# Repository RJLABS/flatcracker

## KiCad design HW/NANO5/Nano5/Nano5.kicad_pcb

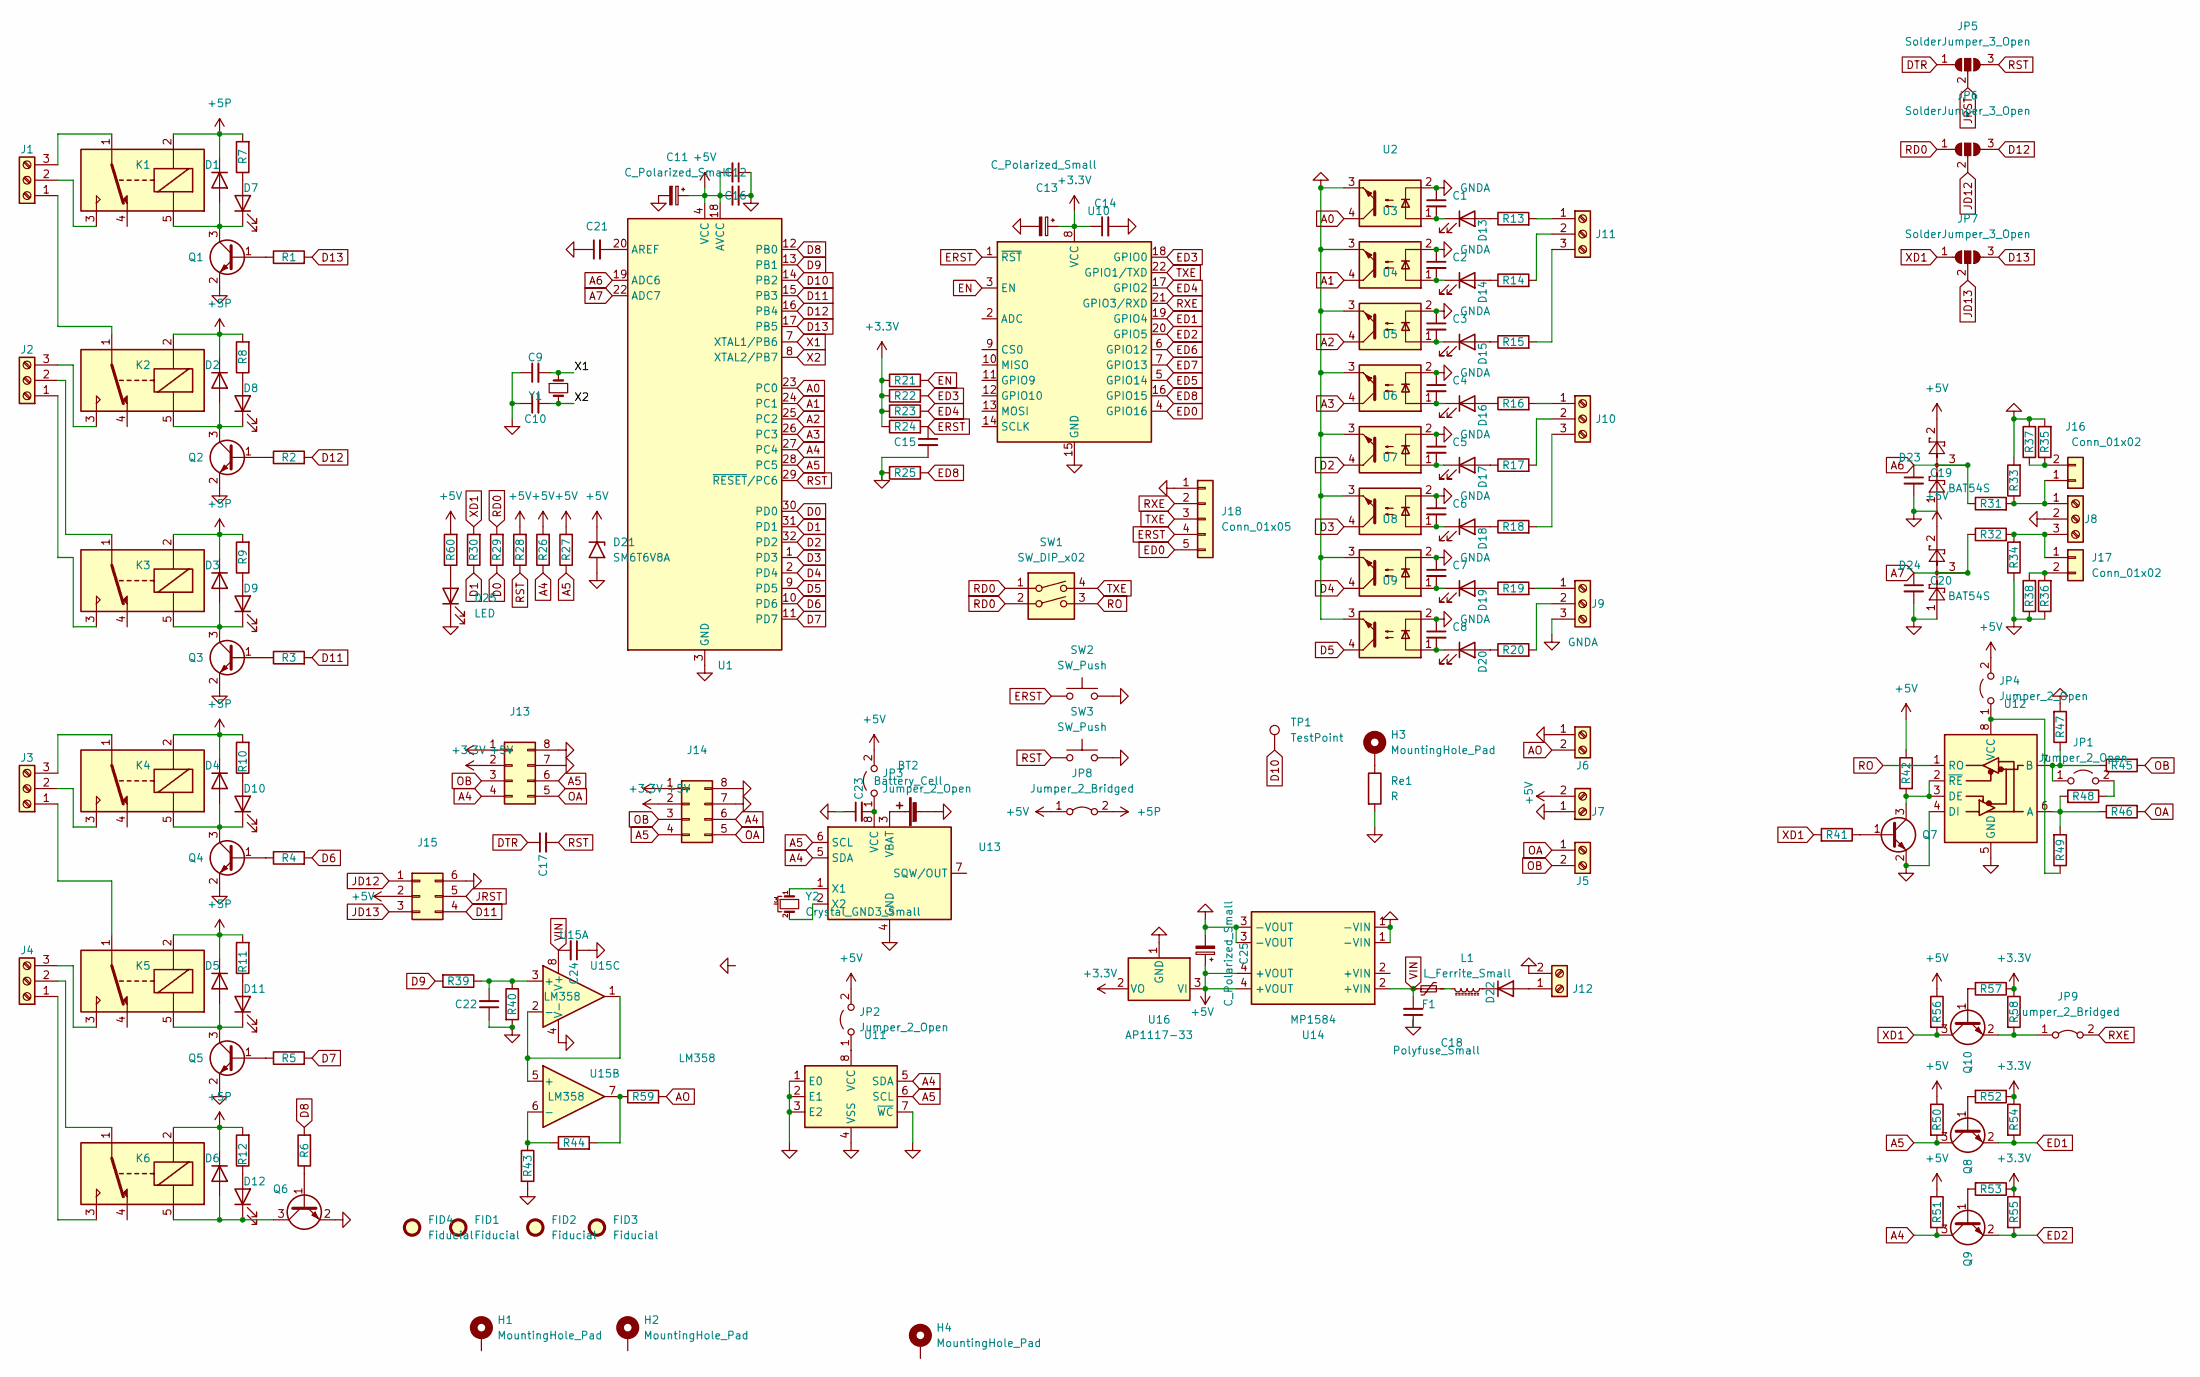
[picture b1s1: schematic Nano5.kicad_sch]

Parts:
BT2: Battery_Cell; BatteryHolder_Keystone_1058_1x2032
C1, C2, C3, C4, C5, C6, C7, C8, C9, C10, C19, C20: C_Small; C_0805_2012Metric
C11, C13, C25: C_Polarized_Small; CP_Elec_4x3.9
C12, C14, C15, C16, C17, C18, C21, C22, C23, C24: 100nF; C_0805_2012Metric
D1, D2, D3, D4, D5, D6, D22: SM4007; D_MELF
D7, D8, D9, D10, D11, D12, D13, D14, D15, D16, D17, D18, D19, D20, D25: LED; LED_0805_2012Metric
D21: SM6T6V8A; D_SMB
D23, D24: BAT54S; SOT-23
F1: Polyfuse_Small; Fuse_1812_4532Metric
FID1, FID2, FID3, FID4: Fiducial; Fiducial_1.5mm_Mask3mm
H1, H2, H3, H4: MountingHole_Pad; MountingHole_3.2mm_M3_Pad_Via
J1, J2, J3, J4, J8, J9, J10, J11: Screw_Terminal_01x03; TerminalBlock_Phoenix_MKDS-1,5-3-5.08_1x03_P5.08mm_Horizont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
J5, J6, J7, J12: Screw_Terminal_01x02; TerminalBlock_Phoenix_MKDS-1,5-2_1x02_P5.00mm_Horizontal
J13, J14: Conn_02x04_Counter_Clockwise; IDC-Header_2x04_P2.54mm_Vertical
J15: Conn_02x03_Counter_Clockwise; IDC-Header_2x03_P2.54mm_Vertical
J16, J17: Conn_01x02; PinHeader_1x02_P2.54mm_Vertical
J18: Conn_01x05; PinHeader_1x05_P2.54mm_Vertical
JP1, JP2, JP3, JP4: Jumper_2_Open; SolderJumper-2_P1.3mm_Open_RoundedPad1.0x1.5mm
JP5, JP6, JP7: SolderJumper_3_Open; SolderJumper-3_P1.3mm_Open_RoundedPad1.0x1.5mm
JP8: Jumper_2_Bridged; SolderJumper-2_P1.3mm_Bridged2Bar_RoundedPad1.0x1.5mm
JP9: Jumper_2_Bridged; SolderJumper-2_P1.3mm_Bridged_RoundedPad1.0x1.5mm
K1, K2, K3, K4, K5, K6: SANYOU_SRD_Form_C; Relay_SPDT_SANYOU_SRD_Series_Form_C
L1: L_Ferrite_Small; L_1806_4516Metric_Pad1.45x1.90mm_HandSolder
Q1, Q2, Q3, Q4, Q5, Q6, Q7, Q8, Q9, Q10: MMBT3904; SOT-23
R1, R2, R3, R4, R5, R6, R7, R8, R9, R10, R11, R12, R13, R14, R15, R16, R17, R18, R19, R20, R21, R22, R23, R24, R25, R26, R27, R28, R29, R30, R31, R32, R33, R34, R35, R36, R39, R40, R41, R42, R43, R44, R45, R46, R47, R48, R49, R50, R51, R52, R53, R54, R55, R56, R57, R58, R59, R60: R; R_0805_2012Metric
R37, R38: R; R_Axial_DIN0204_L3.6mm_D1.6mm_P7.62mm_Horizontal
Re1: R; R_Axial_DIN0207_L6.3mm_D2.5mm_P10.16mm_Horizontal
SW1: SW_DIP_x02; SW_DIP_SPSTx02_Slide_6.7x6.64mm_W8.61mm_P2.54mm_LowProfile
SW2, SW3: SW_Push; SW_SPST_B3U-1000P
TP1: TestPoint; TestPoint_Pad_D1.0mm
U1: ATmega328P-A; TQFP-32_7x7mm_P0.8mm
U2, U3, U4, U5, U6, U7, U8, U9: LTV-817S; SMDIP-4_W9.53mm
U10: ESP-12E
U11: M24C02-RMN; SOIC-8_3.9x4.9mm_P1.27mm
U12: ST485EBDR; SOIC-8_3.9x4.9mm_P1.27mm
U13: DS1307Z+; SOIC-8_3.9x4.9mm_P1.27mm
U14: MP1584; SRT_MPT1584EN_Module
U15: LM358
U16: AP1117-33; SOT-223-3_TabPin2
Y1: Crystal_Small; Crystal_SMD_HC49-SD
Y2: Crystal_GND3_Small; Crystal_SMD_FrontierElectronics_FM206

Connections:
+3V3: C13.1, C14.1, J13.2, J14.2, R21.1, R22.1, R23.1, R24.1, R52.1, R53.1, R54.1, R55.1, R57.1, R58.1, U10.8 (VCC), U16.2 (VO)
+5P: D1.1 (K), D2.1 (K), D3.1 (K), D4.1 (K), D5.1 (K), D6.1 (K), JP8.2 (B), K1.2, K2.2, K3.2, K4.2, K5.2, K6.2, R7.2, R8.2, R9.2, R10.2, R11.2, R12.2
+5V: C11.1, C12.1, C16.2, C25.1, D21.1 (A1), D23.2, D24.2, J7.2, J13.1, J14.1, J15.2, JP2.2 (B), JP3.2 (B), JP4.2 (B), JP8.1 (A), R26.2, R27.2, R28.2, R42.1, R50.1, R51.1, R56.1, R60.2, U1.4 (VCC), U1.6 (VCC), U1.18 (AVCC), U14.4 (+VOUT), U16.3 (VI)
A0: U1.23 (PC0), U2.4
A1: U1.24 (PC1), U3.4
A2: U1.25 (PC2), U4.4
A3: U1.26 (PC3), U5.4
A4: J13.4, J14.6, Q9.3 (C), R26.1, R51.2, U1.27 (PC4), U11.5 (SDA), U13.5 (SDA)
A5: J13.6, J14.4, Q8.3 (C), R27.1, R50.2, U1.28 (PC5), U11.6 (SCL), U13.6 (SCL)
A6: C19.1, D23.3, R31.1, U1.19 (ADC6)
A7: C20.1, D24.3, R32.1, U1.22 (ADC7)
AO: J6.2, R59.2
D0: R29.1, U1.30 (PD0)
D1: R30.1, U1.31 (PD1)
D2: U1.32 (PD2), U6.4
D3: U1.1 (PD3), U7.4
D4: U1.2 (PD4), U8.4
D5: U1.9 (PD5), U9.4
D6: R4.2, U1.10 (PD6)
D7: R5.2, U1.11 (PD7)
D8: R6.2, U1.12 (PB0)
D9: R39.2, U1.13 (PB1)
D10: TP1.1, U1.14 (PB2)
D11: J15.4, R3.2, U1.15 (PB3)
D12: JP6.3 (B), R2.2, U1.16 (PB4)
D13: JP7.3 (B), R1.2, U1.17 (PB5)
DTR: C17.1, JP5.1 (A)
ED0: J18.5, U10.4 (GPIO16)
ED1: Q8.2 (E), R54.2, U10.19 (GPIO4)
ED2: Q9.2 (E), R55.2, U10.20 (GPIO5)
ED3: R22.2, U10.18 (GPIO0)
ED4: R23.2, U10.17 (GPIO2)
ED5: U10.5 (GPIO14)
ED6: U10.6 (GPIO12)
ED7: U10.7 (GPIO13)
ED8: R25.1, U10.16 (GPIO15)
EN: R21.2, U10.3 (EN)
ERST: C15.1, J18.4, R24.2, SW2.1, U10.1 (~RST)
GND: BT2.2 (-), C9.1, C10.1, C11.2, C12.2, C13.2, C14.2, C15.2, C16.1, C18.1, C19.2, C20.2, C21.1, C22.1, C23.1, C24.1, C25.2, D21.2 (A2), D23.1, D24.1, D25.1 (K), J6.1, J7.1, J8.2, J12.2, J13.7, J13.8, J14.7, J14.8, J15.6, J18.1, Q1.2 (E), Q2.2 (E), Q3.2 (E), Q4.2 (E), Q5.2 (E), Q6.2 (E), Q7.2 (E), R25.2, R33.2, R34.1, R35.2, R36.1, R37.2, R38.1, R40.2, R43.2, R47.2, Re1.2, SW2.2, SW3.2, U1.3 (GND), U1.5 (GND), U1.21 (GND), U2.3, U3.3, U4.3, U5.3, U6.3, U7.3, U8.3, U9.3, U10.15 (GND), U11.1 (E0), U11.2 (E1), U11.3 (E2), U11.4 (VSS), U11.7 (~WC), U12.4 (DI), U12.5 (GND), U13.4 (GND), U14.1 (-VIN), U14.3 (-VOUT), U15.4 (V-), U16.1 (GND)
GNDA: C1.1, C2.1, C3.1, C4.1, C5.1, C6.1, C7.1, C8.1, J9.3, U2.2, U3.2, U4.2, U5.2, U6.2, U7.2, U8.2, U9.2
JD12: J15.1, JP6.2 (C)
JD13: J15.3, JP7.2 (C)
JRST: J15.5, JP5.2 (C)
unnamed: BT2.1 (+), U13.3 (VBAT)
unnamed: C1.2, D13.1 (K), U2.1
unnamed: C2.2, D14.1 (K), U3.1
unnamed: C3.2, D15.1 (K), U4.1
unnamed: C4.2, D16.1 (K), U5.1
unnamed: C5.2, D17.1 (K), U6.1
unnamed: C6.2, D18.1 (K), U7.1
unnamed: C7.2, D19.1 (K), U8.1
unnamed: C8.2, D20.1 (K), U9.1
unnamed: C21.2, U1.20 (AREF)
unnamed: C22.2, R39.1, R40.1, U15.3 (+)
unnamed: C23.2, JP3.1 (A), U13.8 (VCC)
unnamed: D1.2 (A), D7.1 (K), K1.5, Q1.3 (C)
unnamed: D2.2 (A), D8.1 (K), K2.5, Q2.3 (C)
unnamed: D3.2 (A), D9.1 (K), K3.5, Q3.3 (C)
unnamed: D7.2 (A), R7.1
unnamed: D8.2 (A), R8.1
unnamed: D9.2 (A), R9.1
unnamed: D4.2 (A), D10.1 (K), K4.5, Q4.3 (C)
unnamed: D10.2 (A), R10.1
unnamed: D5.2 (A), D11.1 (K), K5.5, Q5.3 (C)
unnamed: D11.2 (A), R11.1
unnamed: D6.2 (A), D12.1 (K), K6.5, Q6.3 (C)
unnamed: D12.2 (A), R12.1
unnamed: D13.2 (A), R13.1
unnamed: D14.2 (A), R14.1
unnamed: D15.2 (A), R15.1
unnamed: D16.2 (A), R16.1
unnamed: D17.2 (A), R17.1
unnamed: D18.2 (A), R18.1
unnamed: D19.2 (A), R19.1
unnamed: D20.2 (A), R20.1
unnamed: D22.1 (K), L1.1
unnamed: D22.2 (A), J12.1
unnamed: D25.2 (A), R60.1
unnamed: F1.2, L1.2
unnamed: J1.1, K2.1
unnamed: J1.2, K1.3
unnamed: J1.3, K1.1
unnamed: J2.1, K3.3
unnamed: J2.2, K3.1
unnamed: J2.3, K2.3
unnamed: J3.1, K5.1
unnamed: J3.2, K4.3
unnamed: J3.3, K4.1
unnamed: J4.1, K6.3
unnamed: J4.2, K6.1
unnamed: J4.3, K5.3
unnamed: J9.1, R19.2
unnamed: J9.2, R20.2
unnamed: J10.1, R16.2
unnamed: J10.2, R17.2
unnamed: J10.3, R18.2
unnamed: J11.1, R13.2
unnamed: J11.2, R14.2
unnamed: J11.3, R15.2
unnamed: J8.1, J16.1, R31.2, R33.1
unnamed: J16.2, R35.1, R37.1
unnamed: J8.3, J17.1, R32.2, R34.2
unnamed: J17.2, R36.2, R38.2
unnamed: JP1.1 (A), R45.1, R47.1, U12.7 (B)
unnamed: JP1.2 (B), R48.1
unnamed: JP2.1 (A), U11.8 (VCC)
unnamed: JP4.1 (A), R49.1, U12.8 (VCC)
unnamed: Q1.1 (B), R1.1
unnamed: Q2.1 (B), R2.1
unnamed: Q3.1 (B), R3.1
unnamed: Q4.1 (B), R4.1
unnamed: Q5.1 (B), R5.1
unnamed: Q6.1 (B), R6.1
unnamed: Q7.1 (B), R41.1
unnamed: Q7.3 (C), R42.2, U12.2 (~RE), U12.3 (DE)
unnamed: Q8.1 (B), R52.2
unnamed: Q9.1 (B), R53.2
unnamed: Q10.1 (B), R57.2
unnamed: JP9.1 (A), Q10.2 (E), R58.2
unnamed: R43.1, R44.1, U15.6 (-)
unnamed: R44.2, R59.1, U15.7
unnamed: R46.1, R48.2, R49.2, U12.6 (A)
unnamed: H3.1, Re1.1
unnamed: U13.1 (X1), Y2.1
unnamed: U13.2 (X2), Y2.2
unnamed: U15.1, U15.2 (-), U15.5 (+)
OA: J5.1, J13.5, J14.5, R46.2
OB: J5.2, J13.3, J14.3, R45.2
RD0: JP6.1 (A), R29.2, SW1.1, SW1.2
RO: SW1.3, U12.1 (RO)
RST: C17.2, JP5.3 (B), R28.1, SW3.1, U1.29 (~RESET/PC6)
RXE: J18.2, JP9.2 (B), U10.21 (GPIO3/RXD)
TXE: J18.3, SW1.4, U10.22 (GPIO1/TXD)
VIN: C18.2, C24.2, F1.1, U14.2 (+VIN), U15.8 (V+)
X1: C9.2, U1.7 (XTAL1/PB6), Y1.1
X2: C10.2, U1.8 (XTAL2/PB7), Y1.2
XD1: JP7.1 (A), Q10.3 (C), R30.2, R41.2, R56.2

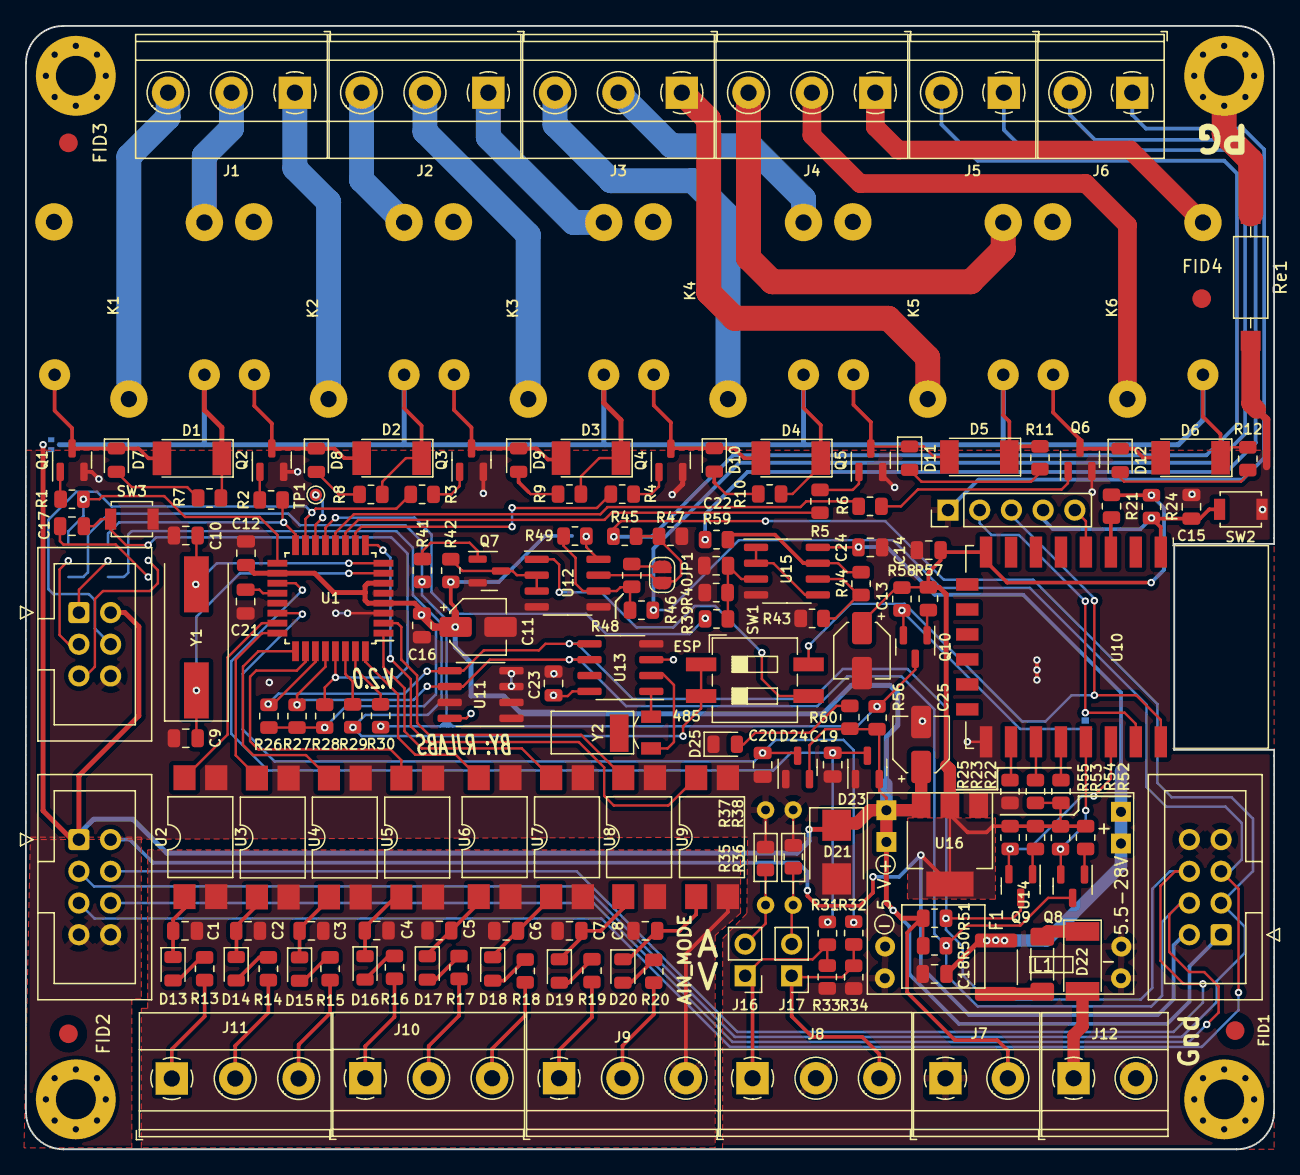
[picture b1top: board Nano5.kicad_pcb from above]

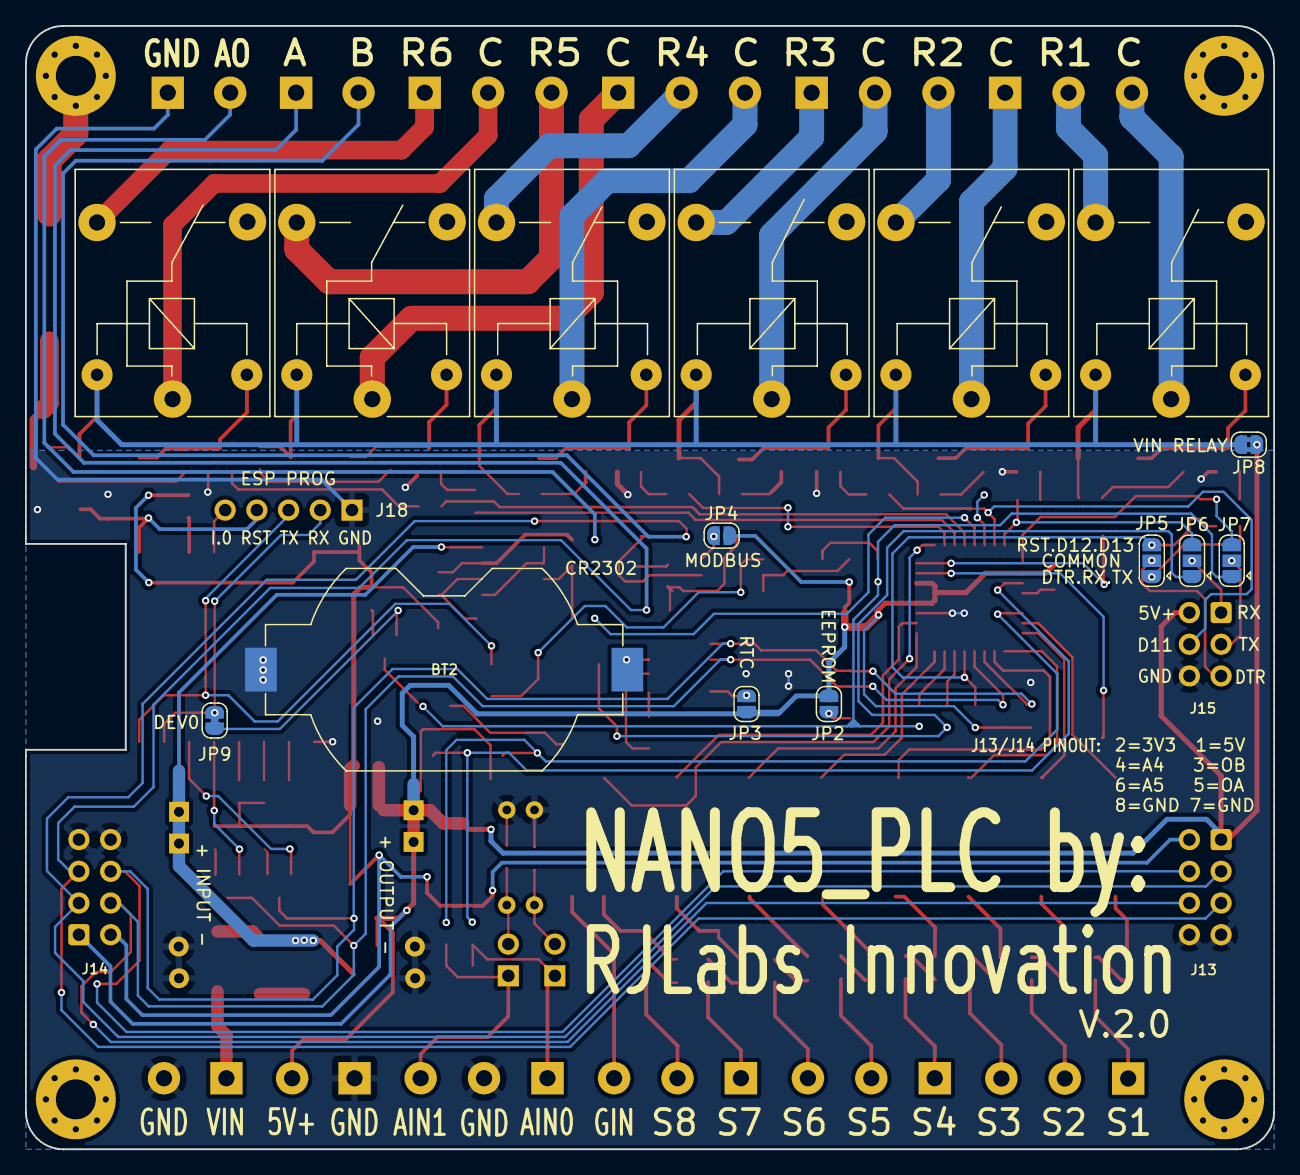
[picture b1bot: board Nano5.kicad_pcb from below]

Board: 2 copper layers, 100.0 x 90.0 mm, 187 parts (9 on the bottom side), 134 nets.

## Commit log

2022-04-07 initial setup
2022-04-09 phase 1
2022-04-10 add mod 1
2022-04-17 MAJOR UPDATE
2022-04-18 Update #auto_saved_files#, Nano5-2022-04-10_203426.zip, and 8 more files...
2022-04-20 update 2104
2022-04-25 fix update
2022-04-27 fix track
2022-05-04 update annote
2025-11-22 update latest
2025-11-22 Fix image syntax in README.md
